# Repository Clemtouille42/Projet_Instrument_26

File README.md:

#  Projet Instrument : Harpe Sans Contact

##  Présentation générale
Ce projet consiste à concevoir et réaliser une harpe électronique sans cordes physiques, dans laquelle les cordes traditionnelles sont remplacées par des faisceaux de détection. Lorsqu'un utilisateur est détecté par le capteur, la harpe analyse la position et la hauteur de la main pour émettre une note de musique spécifique. Ce système reproduit le principe de jeu d'une harpe classique tout en exploitant des technologies modernes de détection et de traitement du signal.

##  Objectifs du projet
* Mettre en œuvre une détection spatiale précise à l'aide d'un capteur multizone.
* Concevoir une carte électronique sur mesure intégrant la gestion d'alimentation et le traitement.
* Traiter les données de distance en temps réel pour les transformer en notes musicales.
* Restituer un signal sonore propre correspondant à la note calculée.

---

##  Architecture du système

Notre architecture repose sur trois grands piliers matériels, de la détection à la restitution sonore, en passant par une gestion rigoureuse de l'énergie.

### 1. Détection des mouvements
* **Capteur Time-of-Flight (ToF) :** VL53L8CX, utilisé pour déterminer avec précision la distance et la position de la main dans l'espace.
* **Adaptation et Communication :** Communication via le bus I2C avec des résistances de Pull-up (4.7 kΩ) sur les lignes SDA/SCL. Un adaptateur de niveaux est prévu pour assurer la compatibilité des signaux entre le capteur et le microcontrôleur.
* **Connectique :** Connecteurs dédiés pour lier physiquement le module capteur à la carte de traitement principale.

### 2. Traitement et Gestion de l'Énergie
* **Microcontrôleur :** STM32G431KB. Il est le cerveau du système : il reçoit les données de position du capteur via I2C et les convertit mathématiquement en notes (ex: mapping de plages de distances vers DO, RE, MI...).
* **Gestion de l'alimentation :** * **Alimentation directe en 5V** via le connecteur USB-C.
  * **Résistances CC (5.1 kΩ) :** Tirées vers la masse (GND) sur les broches CC1 et CC2 pour la négociation de puissance et assurer que le système reçoit bien ses 5V.
  * **LDO (Régulateur de tension) :** Abaisse le 5V en une tension stable de 3.3V, indispensable pour alimenter le microcontrôleur et le capteur ToF.
  * **Filtrage et découplage :** Utilisation de billes de ferrite et de condensateurs de découplage pour garantir une tension propre, sans parasites, afin de ne pas perturber les communications I2C et les traitements internes.

### 3. Restitution du signal
* **Isolation :** Optocoupleur pour garantir l'isolation électrique, protéger le microcontrôleur et éliminer les boucles de masse.
* **Audio :** Le signal est traité par un amplificateur avant d'être envoyé au mini haut-parleur pour la vibration sonore finale.
* **Interface externe :** Prise / Câble MIDI permettant une sortie numérique vers d'autres instruments ou un ordinateur.

---

##  Logiciel Embarqué (Work In Progress)

Le firmware (dossier `/CODE`) est actuellement en cours de développement et de débogage.

* **Communication :** Interfaçage I2C en cours d'implémentation pour récupérer la matrice de données du VL53L8CX.
* **Algorithme prévu :** Découpage du champ de vision du capteur en plusieurs zones virtuelles. Chaque zone correspond à une "corde". La distance mesurée dans une zone détermine la hauteur de la note (Grave/Aiguë) tandis que la zone elle-même détermine la note de la gamme.

---

##  Structure du dépôt

L'arborescence du projet est organisée de la manière suivante :

* 📁 **`Armature harpe/`** : Fichiers liés à la structure mécanique de la harpe (bois, impression 3D).
* 📁 **`CODE/`** : Code source C pour le microcontrôleur STM32 (En cours de développement).
* 📁 **`Commandes/`** : Contien les resource concernant la conception du pcb.
* 📁 **`Composants/`** : Regroupe toutes les ressources matérielles brutes (Datasheets des composants, empreintes spécifiques, nomenclature complète `composants.xlsx`).
* 📁 **`KiCad Harpe/`** : Projet KiCad complet incluant les schémas électroniques et le routage du PCB de notre carte sur mesure.
Pour plus de détaille lire les readme des sous parties.
---

##  L'Équipe

Projet réalisé dans le cadre de notre 1ère année de cycle ingénieur (ENSEA) par :

* **Clément SERVAES** - Le Grand Manitou
* **Damien GANTCHEV** - Le Grand Vizir
* **Serge AROU** - Le Grand Chanteur
* **Maxime LEBRUN** - Le Grand Brun

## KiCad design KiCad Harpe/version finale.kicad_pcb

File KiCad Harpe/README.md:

Ce fichier contient les schémas et le PCB réalisés sur KiCad, ainsi que les fichiers Gerber utilisés pour la commande du PCB chez JLCPCB.

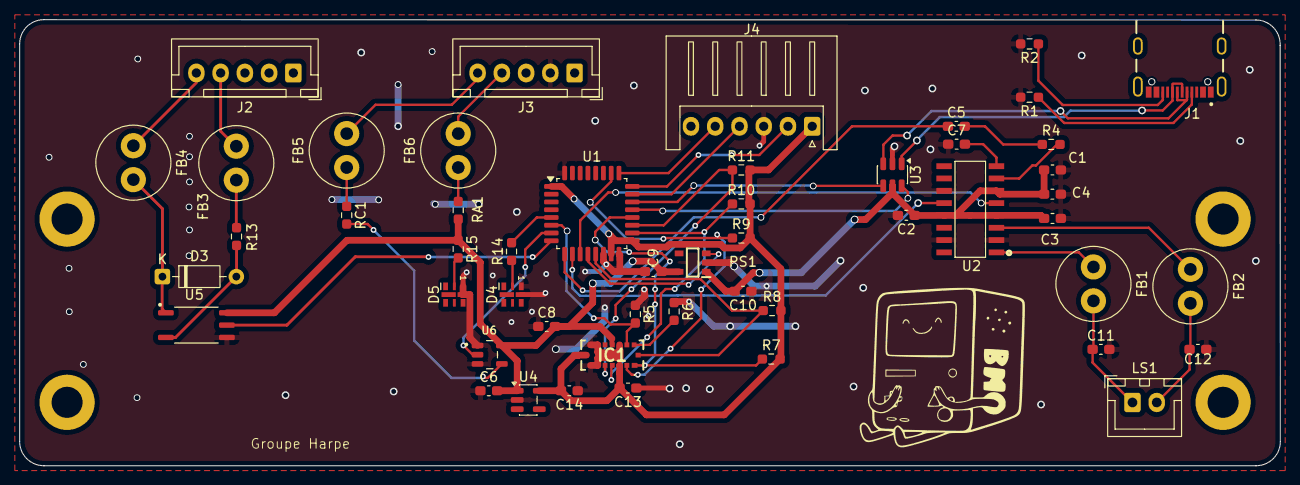
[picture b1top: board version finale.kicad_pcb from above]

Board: 2 copper layers, 130.0 x 46.0 mm, 51 parts (0 on the bottom side), 46 nets.

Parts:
C1: 470uF; C_0603_1608Metric_Pad1.08x0.95mm_HandSolder
C2, C3, C4, C6, C7, C9, C10, C14: 1uF; C_0603_1608Metric_Pad1.08x0.95mm_HandSolder
C5: 0.47uF; C_0603_1608Metric_Pad1.08x0.95mm_HandSolder
C8: 4,7uF; C_0603_1608Metric_Pad1.08x0.95mm_HandSolder
C11, C12: 220pF; C_0603_1608Metric_Pad1.08x0.95mm_HandSolder
C13: 100nF; C_0603_1608Metric_Pad1.08x0.95mm_HandSolder
D3: 1N914; D_DO-35_SOD27_P7.62mm_Horizontal
D4, D5: LED; LED-APA102-2020
FB1, FB2: 300 Ohm / 100MHz; L_Radial_D7.5mm_P3.50mm_Fastron_07P
FB3, FB4, FB5, FB6: 1K@100MHz; L_Radial_D7.5mm_P3.50mm_Fastron_07P
IC1: VL53L8CXV9GC_1
J1: USB_C_Receptacle_USB2.0_16P; GCT_USB4105-GF-A
J2, J3: Conn_01x05_Pin; JST_XH_B5B-XH-A_1x05_P2.50mm_Vertical
J4: Conn_01x06_Pin; JST_XH_S6B-XH-A_1x06_P2.50mm_Horizontal
LS1: Speaker; JST_XH_B2B-XH-A_1x02_P2.50mm_Vertical
PS1: BU33SD5WG-TR
R1, R2: 5,1k; R_0603_1608Metric_Pad0.98x0.95mm_HandSolder
R4: 18k; R_0603_1608Metric_Pad0.98x0.95mm_HandSolder
R5, R6, R7, R8, R9: 47k; R_0603_1608Metric_Pad0.98x0.95mm_HandSolder
R10, R11: 2.2k; R_0603_1608Metric_Pad0.98x0.95mm_HandSolder
R13: 220; R_0603_1608Metric_Pad0.98x0.95mm_HandSolder
R14, R15: 1k; R_0603_1608Metric_Pad0.98x0.95mm_HandSolder
RA1: 33; R_0603_1608Metric_Pad0.98x0.95mm_HandSolder
RC1: 10; R_0603_1608Metric_Pad0.98x0.95mm_HandSolder
U1: STM32G431KBTx; LQFP-32_7x7mm_P0.8mm
U2: PAM8403DR
U3: USBLC6-2SC6; SOT-23-6
U4: AP2112K-1.8; SOT-23-5
U5: ACPL-M61L-000E; ACPL-M50L-000E
U6: 74LVC1G125; SN74AHCT1G125DBVR

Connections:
+3.3V: C6.2, C8.2, C9.2, IC1.C4 (AVDD), PS1.5 (VOUT), R15.1, RA1.2, U4.1 (VIN), U5.6 (VDD), U6.5 (VCC)
+5V: C1.1, C2.1, C3.1, C4.2, C10.2, PS1.1 (VIN), U2.4 (PVDD@1), U2.6 (VDD), U2.13 (PVDD@2), U3.5 (VBUS)
+OUT_L: FB1.1, U2.1 (+OUT_L)
-OUT_L: FB2.1, U2.3 (-OUT_L)
ANODE: D3.1 (K), FB4.2, U5.1 (ANODE)
CATHODE: D3.2 (A), R13.2, U5.3 (CATHODE)
Data_N1: J1.A6 (D+), J1.B6 (D+), U3.1 (I/O1)
Data_N2: U1.21 (PA11), U3.6 (I/O1)
Data_P1: J1.A7 (D-), J1.B7 (D-), U3.3 (I/O2)
Data_P2: U1.22 (PA12), U3.4 (I/O2)
GND: C1.2, C2.2, C3.2, C4.1, C6.1, C7.1, C8.1, C9.1, C10.1, C11.2, C12.1, C13.1, C14.1, D4.1 (K), D5.1 (K), IC1.A6 (RSVD1), IC1.A7 (RSVD2), IC1.B4 (GROUND_1), IC1.C3 (GND), IC1.C6 (RSVD3), IC1.C7 (GROUND_2), J3.2, J4.3, PS1.2 (GND), R1.2, R2.2, R5.1, R6.1, U1.14 (VSSA), U1.16 (VSS), U1.32 (VSS), U2.2 (PGND@1), U2.11 (GND), U2.15 (PGND@2), U3.2 (GND), U4.2 (GND), U5.4 (GND), U6.1, U6.3 (GND)
INL: C5.1, U1.9 (PA4)
INT: IC1.A1 (INT), R7.1, U1.20 (PA10)
IOVDD: C13.2, C14.2, IC1.A3 (IOVDD), IC1.B7 (CORE_1V8), J4.1, R7.2, R8.2, R9.2, R10.2, R11.2, U1.1 (VDD), U1.15 (VDDA), U1.17 (VDD), U4.5 (VOUT)
LPn_EN_COM: IC1.A2 (LPN), R9.1, U1.26 (PB3)
MUTE: U1.11 (PA6), U2.5 (MUTE)
NCS: IC1.C2 (NCS), R5.2, U1.6 (PA1)
unnamed: C5.2, R4.1
unnamed: C11.1, FB1.2, LS1.1
unnamed: C12.2, FB2.2, LS1.2
unnamed: D4.2 (A), R14.1
unnamed: D5.2 (A), R15.2
unnamed: FB3.1, R13.1
unnamed: FB5.1, RC1.1
unnamed: FB6.1, RA1.1
unnamed: IC1.C1 (SPI_I2C_N), R6.2
unnamed: J1.A5 (CC1), R1.1
unnamed: J1.B5 (CC2), R2.1
unnamed: FB3.2, J2.4
unnamed: FB4.1, J2.5
unnamed: FB6.2, J3.4
unnamed: FB5.2, J3.5
unnamed: R4.2, U2.7 (INL)
unnamed: C7.2, U2.8 (VREF)
RC: RC1.2, U6.4
SCL: IC1.A5 (SCL/MCLK), R11.1, U1.19 (PA9)
SDA: IC1.A4 (SDA_/_MOSI), R10.1, U1.18 (PA8)
SHDN: U1.10 (PA5), U2.12 (SHND)
STBY: PS1.3 (STBY), U1.12 (PA7)
SWDIO: J4.4, U1.23 (PA13)
SW_Reset: J4.5, U1.25 (PA15)
SYNC: IC1.B1 (SYNC), R8.1, U1.13 (PB0)
SYS_LED: R14.2, U1.5 (PA0)
UART RX: U1.8 (PA3), U5.5 (VO)
UART TX: U1.7 (PA2), U6.2
WSCLK: J4.2, U1.24 (PA14)

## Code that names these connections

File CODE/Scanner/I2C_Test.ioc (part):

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Mcu.Name=STM32G431K(6-8-B)Tx
Mcu.Package=LQFP32
Mcu.UserName=STM32G431KBTx
PA13.Mode=Serial_Wire
PA13.Signal=SYS_JTMS-SWDIO
PA14.Mode=Serial_Wire
PA14.Signal=SYS_JTCK-SWCLK
PA8.Mode=I2C
PA8.Signal=I2C2_SDA
PA9.Mode=I2C
PA9.Signal=I2C2_SCL
RCC.HSE_VALUE=8000000
RCC.SYSCLKFreq_VALUE=16000000
board=custom

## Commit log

2026-02-02 Create Hardware
    Tout ce qui concerne les composants / PCB
2026-02-02 Create Hardware
2026-02-02 Create Liste_des_composants
2026-02-02 Liste de composant
2026-02-02 Create cacaprout
2026-02-02 Add Motion Sensor VL53L8CX to component list
2026-02-02 Add files via upload
    Lidar 2d
2026-02-02 Add STM32G431KB microcontroller to components list
2026-02-02 Update Liste_des_composants
2026-02-06 Add transformer information to component list
2026-02-06 Add USB-C and MIDI components to the list
2026-02-09 Update component list by removing entries
    Removed 'Haut Parleur' and 'Cable MIDI' entries from the component list.
2026-02-16 Rename composants (2).xlsx to composants.xlsx
2026-05-11 Create PCB et Gerber
2026-05-11 Create ...
2026-05-12 Add files via upload
    Fichier drill + gerber pour la commande JLpcb
2026-05-21 Create CODE
    Ici se trouve la partie logicielle du projet. Cela comprend :
    * Programme brut
    * Description de l’avancée du projet et des objectifs
2026-05-21 Add files via upload
    SDK du Lidar
2026-05-21 Add files via upload
    le VLCX pour les nuls
2026-05-21 Revise README with updated project details and objectives
    Updated project description and objectives to reflect changes in sensor technology and system architecture.
2026-05-21 Create Capteur I2C
2026-05-24 Enhance README with project development details
    Added detailed project report covering development, programming choices, I2C communication tests, memory limitations, and future perspectives.
